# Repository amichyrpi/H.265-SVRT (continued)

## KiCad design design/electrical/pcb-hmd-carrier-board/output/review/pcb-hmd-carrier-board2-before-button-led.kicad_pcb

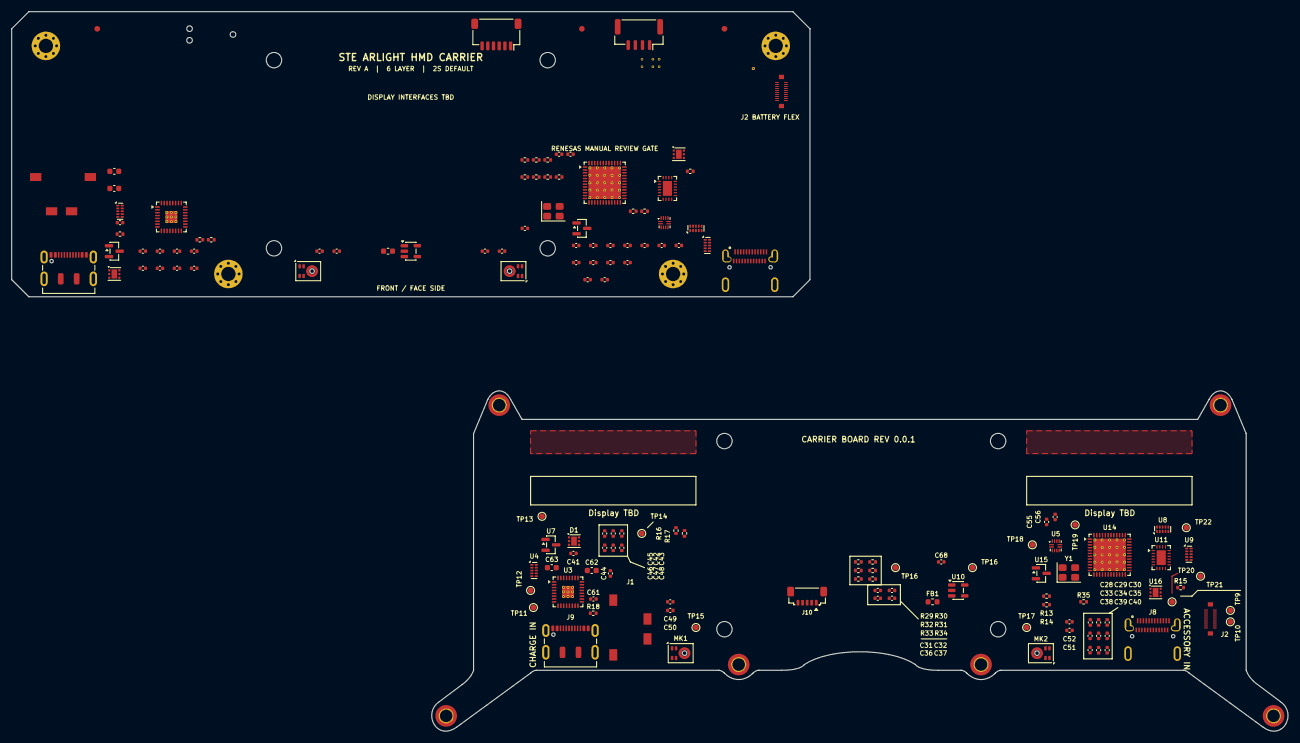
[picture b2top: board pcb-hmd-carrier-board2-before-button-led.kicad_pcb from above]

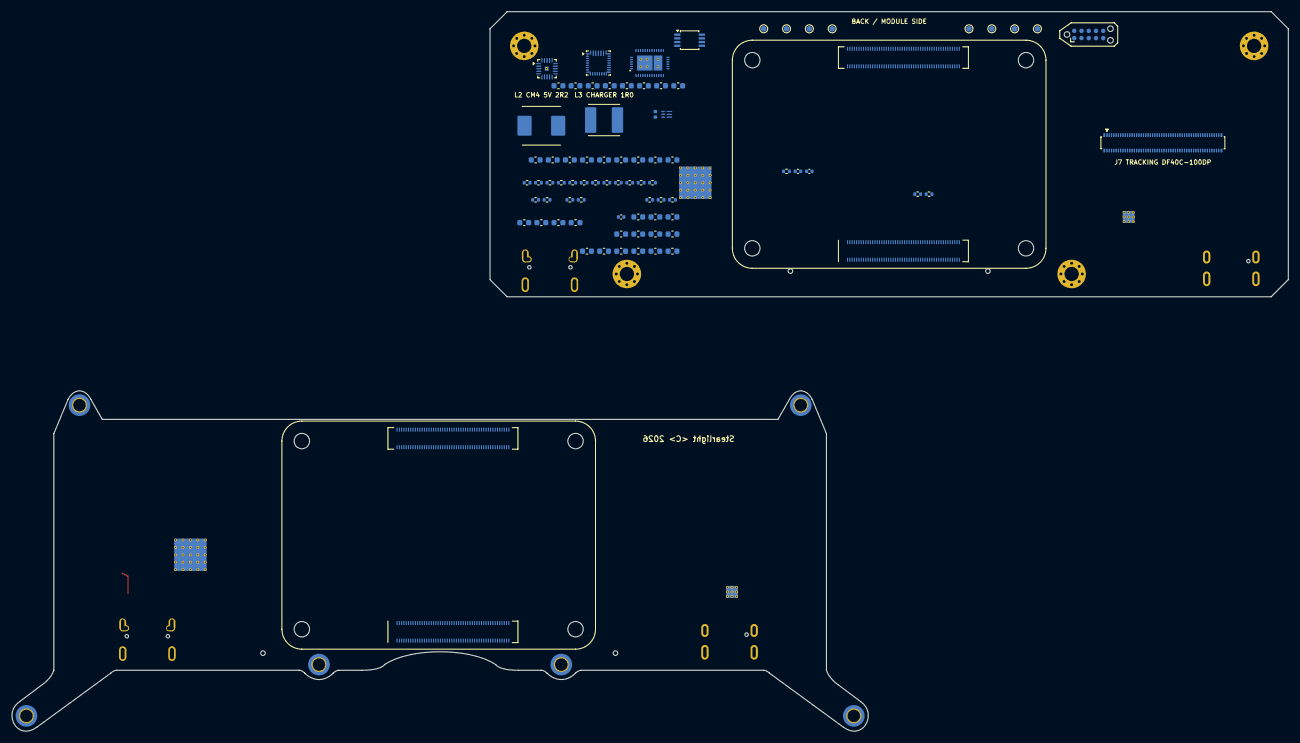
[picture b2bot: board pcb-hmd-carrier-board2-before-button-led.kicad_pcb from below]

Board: 6 copper layers, 223.8 x 126.2 mm, 232 parts (79 on the bottom side), 120 nets, no tracks yet.

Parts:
C1, C2, C3, C4, C5, C9, C10, C11, C13, C14, C19, C20, C21, C22, C23: 10u; C_0603_1608Metric
C6, C12, C15, C24, C25: 100n; C_0603_1608Metric
C7, C8: 330p; C_0603_1608Metric
C16: 4u7; C_0603_1608Metric
C17, C18: 47n; C_0603_1608Metric
C26: 1u; C_0603_1608Metric
C27: 47p; C_0603_1608Metric
C28, C28#2, C29, C29#2, C30, C30#2, C31, C31#2, C32, C32#2, C33, C33#2, C34, C34#2, C35, C35#2, C36, C36#2, C37, C37#2, C43, C43#2, C48, C48#2: 100n; C_0402_1005Metric
C38, C38#2, C44, C44#2, C45, C45#2, C46, C46#2, C47, C47#2: 10u; C_0402_1005Metric
C39, C39#2, C40, C40#2, C41, C41#2, C42, C42#2: 1u; C_0402_1005Metric
C49, C49#2, C50, C50#2, C51, C51#2, C52, C52#2: 1u C0G; C_0402_1005Metric
C53, C54, C55, C55#2, C56, C56#2: 100n PCIe AC; C_0402_1005Metric
C57, C58: 100u low-ESR; C_0603_1608Metric
C59, C60: 22u 25V; C_0603_1608Metric
C61, C61#2: 100n JACK MIC; C_0402_1005Metric
C62, C62#2: 47u HP LEFT; C_0603_1608Metric
C63, C63#2: 47u HP RIGHT; C_0603_1608Metric
C64: 4.7u 10V; C_0603_1608Metric
C65, C66: 10u 6.3V; C_0603_1608Metric
C67: 120p C0G; C_0402_1005Metric
C68, C68#2: 100n USB3 RESET; C_0402_1005Metric
D1, D1#2: TVS2200DRVR; WSON-6-1EP_2x2mm_P0.65mm_EP1x1.6mm
FB1, FB1#2: 600R@100MHz ferrite; L_0603_1608Metric
FID1, FID2, FID3: FIDUCIAL; Fiducial_1mm_Mask2mm
H1, H2, H3, H4: M2.5; MountingHole_2.5mm_Pad_Via
J1, J1#2: SJ-43514-SMT-TR; SameSky_SJ-43514-SMT-TR
J2, J2#2: BM28 BATTERY FLEX 5A + NTC/ID; Hirose_BM28B0.6-20DS_2-0.35V
J4: 5V GND PWM TACH; JST_GH_SM04B-GHS-TB_1x04-1MP_P1.25mm_Horizontal
J5: 3V3 GND SDA SCL INT GPIO; JST_SH_SM06B-SRSS-TB_1x06-1MP_P1.00mm_Horizontal
J6: TAG-CONNECT SERVICE PADS (NO FIT); Tag-Connect_TC2050-IDC-NL_2x05_P1.27mm_Vertical
J7: DF40C-100DP-0.4V(51) TRACKING; Hirose_DF40C-100DP-0.4V_2x50-1MP_P0.4mm
J8, J8#2: DX07S024JJ2R1300 ACCESSORY; JAE_DX07S024JJ2R1300
J9, J9#2: DX07S016JA1R1500 CHARGE/SERVICE; USB_C_Receptacle_JAE_DX07S016JA1R1500
J10: PROX SENSOR - SM05B-SURS-TF; JST_SUR_SM05B-SURS-TF_1x05-1MP_P0.80mm_Horizontal
L1: 0.47uH XFL4015-471MEC; L_0402_1005Metric
L2: SRP7050TA-2R2M 2.2uH 10A; Bourns_SRP7050TA
L3: SRP5030CA-1R0M 1uH 9A; Bourns_SRP5030CA
MK1, MK1#2, MK2, MK2#2: IM73A135V01; Infineon_PG-LLGA-5-2
Module1, Module1#2: CM4 2GB/16GB/Wireless; Raspberry-Pi-4-Compute-Module
R1: 220k; R_0402_1005Metric
R2: 30k; R_0402_1005Metric
R3: 5.23k ILIM; R_0402_1005Metric
R4: 137k ILIM; R_0402_1005Metric
R5, R6: 2.2k I2C; R_0402_1005Metric
R7, R8: 10k; R_0402_1005Metric
R9: 30.1k TS; R_0402_1005Metric
R10: 10k NTC; R_0402_1005Metric
R11: 100R BATP; R_0402_1005Metric
R12: 6.04k 2S; R_0402_1005Metric
R13, R13#2, R14, R14#2: 200k; R_0402_1005Metric
R15, R15#2: ILIM 1.5A TBD; R_0402_1005Metric
R16, R16#2, R17, R17#2: I2C 2.2k; R_0402_1005Metric
R18, R18#2: MICBIAS 2.7k; R_0402_1005Metric
R19: 75k 1V05 FB; R_0402_1005Metric
R20: 100k 1V05 FB; R_0402_1005Metric
R21: 100k 1V05 PG; R_0402_1005Metric
R22: 10k WIFI EN; R_0402_1005Metric
R23: 10k BT EN; R_0402_1005Metric
R24: 75k MODE; R_0402_1005Metric
R25: 51k MODE; R_0402_1005Metric
R26: 10k CLKREQ; R_0402_1005Metric
R27: 2.2k CHG SCL; R_0402_1005Metric
R28: 2.2k CHG SDA; R_0402_1005Metric
R29, R29#2: 10k OCI PU; R_0402_1005Metric
R30, R30#2: 1.6k RREF VERIFY; R_0402_1005Metric
R31, R31#2: 10k RESET PU; R_0402_1005Metric
R32, R32#2: 10k SPI CLK PD; R_0402_1005Metric
R33, R33#2: 10k SPI CS PD; R_0402_1005Metric
R34, R34#2: 10k SPI MISO PU; R_0402_1005Metric
R35, R35#2: 10k SPI MOSI PD; R_0402_1005Metric
TP1, TP9, TP10, TP11, TP12, TP13, TP14, TP15, TP16, TP16#2, TP17, TP18, TP19, TP20, TP21, TP22: CHG_STAT; TestPoint_Pad_D1.0mm
TP2: PGOOD_5V; TestPoint_Pad_D1.0mm
TP3: BAT_ID; TestPoint_Pad_D1.0mm
TP4: +5V_SYS; TestPoint_Pad_D1.0mm
TP5: +3V3; TestPoint_Pad_D1.0mm
TP6: +1V05_USB; TestPoint_Pad_D1.0mm
TP7: GND; TestPoint_Pad_D1.0mm
TP8: VBAT_SYS; TestPoint_Pad_D1.0mm
U1: TPS62825DMQR; Texas_DMQ0006A_VSON-HR-6_1.5x1.5mm
U2: TPS568230RJER; Texas_RJE0020A_VQFN-20-1EP_3x3mm_P0.45mm_EP0.675x0.76mm_The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
U3, U3#2: TLV320AIC3204IRHBR; Texas_RHB0032M_VQFN-32-1EP_5x5mm_P0.5mm_EP2.1x2.1mm_Thermal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
U4, U4#2: TPD4E05U06DQAR; USON-10_2.5x1.0mm_P0.5mm
U5, U5#2: TUSB320LAIRWBR; Texas_X2QFN-12_1.6x1.6mm_P0.4mm
U6: BQ25798RQMR; Texas_RQM0029A_VQFN-29_4x4mm_P0.4mm
U7, U7#2: TPD2EUSB30DRTR; SOT-23
U8, U8#2, U9, U9#2: TPD4EUSB30DQAR; USON-10_2.5x1.0mm_P0.5mm
U10, U10#2: TLV75528PDBVR; SOT-23-5
U11, U11#2: HD3SS3212IRKSR; Texas_RVC0020A_WQFN-20-1EP_3x4mm_P0.5mm_EP1.6x2.6mm
U12: TPS25751DREFR; Texas_REF0038A_WQFN-38_6x4mm_DualPad
U13: CAT24C512WI-GT3; TSSOP-8_3x3mm_P0.65mm
U14, U14#2: UPD720202K8-711-BAA-A; QFN-48-1EP_7x7mm_P0.5mm_EP5.7x5.7mm_ThermalVias
U15, U15#2: TLV803EA30DBZR; SOT-23
U16, U16#2: TPS2553-1DRVR; WSON-6-1EP_2x2mm_P0.65mm_EP1x1.6mm
Y1, Y1#2: 24MHz; Crystal_SMD_3225-4Pin_3.2x2.5mm

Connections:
+1V05_USB: C28.1, C28#2.1, C29.1, C29#2.1, C30.1, C30#2.1, C31.1, C31#2.1, C32.1, C32#2.1, C33.1, C33#2.1, C39.1, C39#2.1, C65.1, C66.1, C67.1, L1.2, R19.1, TP6.1, U14.6, U14.9, U14.21, U14.30, U14.33, U14.39, U14.42, U14#2.6, U14#2.9, U14#2.21, U14#2.30, U14#2.33, U14#2.39, U14#2.42
+2V8_MIC: C42.1, C42#2.1, MK1.2, MK1#2.2, MK2.2, MK2#2.2, U10.5, U10#2.5
+3V3: C3.1, C34.1, C34#2.1, C35.1, C35#2.1, C36.1, C36#2.1, C37.1, C37#2.1, C38.1, C38#2.1, C40.1, C40#2.1, C43.1, C43#2.1, C64.1, C68.1, C68#2.1, FB1.1, FB1#2.1, J5.1, J6.1, J10.4, Module1#2.78, Module1#2.84, Module1#2.86, R8.1, R13.1, R13#2.1, R14.1, R14#2.1, R16.1, R16#2.1, R17.1, R17#2.1, R21.1, R22.1, R23.1, R26.1, R29.1, R29#2.1, R31.1, R31#2.1, R34.1, R34#2.1, TP5.1, U1.1, U1.6, U3.6, U3.30, U3#2.6, U3#2.30, U5.3, U5.12, U5#2.3, U5#2.12, U11.6, U11#2.6, U12.38, U14.3, U14.12, U14.22, U14.25, U14.34, U14.43, U14#2.3, U14#2.12, U14#2.22, U14#2.25, U14#2.34, U14#2.43, U15.3, U15#2.3
+3V3_AUDIO: C41.1, C41#2.1, C45.1, C45#2.1, C48.1, C48#2.1, FB1.2, FB1#2.2, U3.26, U3#2.26, U10.1, U10.3, U10#2.1, U10#2.3
+5V_SYS: C57.1, C58.1, J4.1, L2.2, Module1#2.77, Module1#2.79, Module1#2.81, Module1#2.83, Module1#2.85, Module1#2.87, R1.1, TP4.1, U12.34, U12.35, U16.6, U16#2.6
AUDIO_1V8_LDO: C44.1, C44#2.1, U3.24, U3.29, U3#2.24, U3#2.29
AUDIO_MCLK: Module1#2.54, U3.1, U3#2.1
AUDIO_REF: C46.1, C46#2.1, U3.18, U3#2.18
AUDIO_RESET_N: Module1#2.34, U3.31, U3#2.31
BAT+: C24.1, J2.P1, R11.2, U6.22, U6.23
BATP: R11.1, U6.18
BAT_ID: J2.2, TP3.1
BST1: C17.1, U6.4
BST2: C18.1, U6.19
BST_5V: C25.1, U2.1
BT_ENABLE_N: Module1#2.91, R23.2
CC1: C7.1, J8#2.A5, J9#2.A5, U5.1, U5#2.1, U12.28
CC2: C8.1, J8#2.B5, J9#2.B5, U5.2, U5#2.2, U12.29
CHASSIS_GND: J8#2.SH, J9#2.SH
CHG_IRQ_N: R8.2, U6.21, U12.18
CHG_SCL: R27.2, U6.14, U12.17
CHG_SDA: R28.2, U6.15, U12.16
CHG_STAT: TP1.1, U6.1
CM4_EXT_RESET_N: J6.8, Module1#2.100
EMMC_BOOT_N: J6.7, Module1#2.93
FAN_PWM: J4.3, Module1#2.31
FAN_TACH: J4.4, Module1#2.30
FB_5V: C27.1, R1.2, R2.1, U2.14
GND: C1.2, C2.2, C3.2, C4.2, C5.2, C6.2, C7.2, C8.2, C9.2, C10.2, C11.2, C12.2, C13.2, C14.2, C15.2, C16.2, C19.2, C20.2, C21.2, C22.2, C23.2, C24.2, C26.2, C27.2, C28.2, C28#2.2, C29.2, C29#2.2, C30.2, C30#2.2, C31.2, C31#2.2, C32.2, C32#2.2, C33.2, C33#2.2, C34.2, C34#2.2, C35.2, C35#2.2, C36.2, C36#2.2, C37.2, C37#2.2, C38.2, C38#2.2, C39.2, C39#2.2, C40.2, C40#2.2, C41.2, C41#2.2, C42.2, C42#2.2, C43.2, C43#2.2, C44.2, C44#2.2, C45.2, C45#2.2, C46.2, C46#2.2, C47.2, C47#2.2, C48.2, C48#2.2, C57.2, C58.2, C59.2, C60.2, C64.2, C65.2, C66.2, C68.2, C68#2.2, D1.1, D1.2, D1.3, D1.7, D1#2.1, D1#2.2, D1#2.3, D1#2.7, J1#2.4, J2.P2, J4.2, J5.2, J6.2, J6.10, J8#2.A1, J8#2.A12, J8#2.B1, J8#2.B12, J9#2.A1, J9#2.A12, J9#2.B1, J9#2.B12, J10.5, MK1.4, MK1.5, MK1#2.4, MK1#2.5, MK2.4, MK2.5, MK2#2.4, MK2#2.5, Module1#2.1, Module1#2.2, Module1#2.7, Module1#2.8, Module1#2.13, Module1#2.14, Module1#2.22, Module1#2.23, Module1#2.32, Module1#2.33, Module1#2.42, Module1#2.43, Module1#2.52, Module1#2.53, Module1#2.59, Module1#2.60, Module1#2.65, Module1#2.66, Module1#2.71, Module1#2.74, Module1#2.98, Module1#2.101, Module1#2.107, Module1#2.108, Module1#2.113, Module1#2.114, Module1#2.119, Module1#2.120, Module1#2.125, Module1#2.126, Module1#2.131, Module1#2.132, Module1#2.137, Module1#2.138, Module1#2.144, Module1#2.150, Module1#2.155, Module1#2.156, Module1#2.161, Module1#2.162, Module1#2.167, Module1#2.168, Module1#2.173, Module1#2.174, Module1#2.179, Module1#2.180, Module1#2.185, Module1#2.186, Module1#2.191, Module1#2.192, Module1#2.197, Module1#2.198, R2.2, R4.2, R9.2, R10.2, R12.2, R15.2, R15#2.2, R20.2, R25.2, R30.2, R30#2.2, R32.2, R32#2.2, R33.2, R33#2.2, R35.2, R35#2.2, TP7.1, U1.4, U2.7, U2.8, U2.13, U2.18, U2.21, U3.7, U3.12, U3.17, U3.28, U3#2.7, U3#2.12, U3#2.17, U3#2.28, U4.3, U4.5, U4.8, U4#2.3, U4#2.5, U4#2.8, U5.5, U5.10, U5.11, U5#2.5, U5#2.10, U5#2.11, U6.10, U6.11, U6.12, U6.13, U6.27, U7.3, U7#2.3, U8.3, U8.8, U8#2.3, U8#2.8, U9.3, U9.8, U9#2.3, U9#2.8, U10.2, U10#2.2, U11.2, U11.5, U11.11, U11.20, U11#2.2, U11#2.5, U11#2.11, U11#2.20, U12.11, U12.12, U12.14, U12.31, U12.39, U13.1, U13.2, U13.3, U13.4, U13.7, U14.27, U14.49, U14#2.27, U14#2.49, U15.1, U15#2.1, U16.5, U16.7, U16#2.5, U16#2.7, Y1.2, Y1.4, Y1#2.2, Y1#2.4
HP_L: C62.2, C62#2.2, J1#2.2, U4.1, U4#2.1
HP_L_CODEC: C62.1, C62#2.1, U3.25, U3#2.25
HP_R: C63.2, C63#2.2, J1#2.3, U4.2, U4#2.2
HP_R_CODEC: C63.1, C63#2.1, U3.27, U3#2.27
I2C_SCL: J5.4, J6.4, J10.3, Module1#2.56, R16.2, R16#2.2, U3.9, U3#2.9, U5.8, U5#2.8
I2C_SDA: J5.3, J6.3, J10.2, Module1#2.58, R17.2, R17#2.2, U3.10, U3#2.10, U5.7, U5#2.7
I2Ct_SCL: R6.2, U12.9, U13.6
I2Ct_SDA: R5.2, U12.8, U13.5
I2S_BCLK: Module1#2.49, U3.2, U3#2.2
I2S_DIN: Module1#2.27, U3.5, U3#2.5
I2S_DOUT: Module1#2.25, U3.4, U3#2.4
I2S_LRCLK: Module1#2.26, U3.3, U3#2.3
ILIM_HIZ: R3.2, R4.1, U6.17
JACK_MIC: C61.1, C61#2.1, J1#2.1, R18.2, R18#2.2, U4.4, U4#2.4
JACK_MIC_CODEC: C61.2, C61#2.2, U3.21, U3#2.21
LDO_1V5: C2.1, U12.2, U12.3, U12.4
LDO_3V3: C1.1, R5.1, R6.1, R7.1, R27.1, R28.1, U12.1, U13.8
MICBIAS: C47.1, C47#2.1, R18.1, R18#2.1, U3.19, U3#2.19
MIC_L_N: C50.2, C50#2.2, U3.16, U3#2.16
MIC_L_P: C49.2, C49#2.2, U3.15, U3#2.15
MIC_L_RAW_N: C50.1, C50#2.1, MK1.3, MK1#2.3
MIC_L_RAW_P: C49.1, C49#2.1, MK1.1, MK1#2.1
MIC_R_N: C52.2, C52#2.2, U3.13, U3#2.13
MIC_R_P: C51.2, C51#2.2, U3.14, U3#2.14
MIC_R_RAW_N: C52.1, C52#2.1, MK2.3, MK2#2.3
MIC_R_RAW_P: C51.1, C51#2.1, MK2.1, MK2#2.1
MODE_5V: R24.2, R25.1, U2.15
PCIE_CLKREQ_N: Module1#2.102, R26.2, U14.10, U14#2.10
PCIE_CLK_N: Module1#2.112, U14.2, U14#2.2
PCIE_CLK_P: Module1#2.110, U14.1, U14#2.1
PCIE_RST_N: Module1#2.109, U14.47, U14#2.47
PCIE_RX_N: C56.2, C56#2.2, Module1#2.118
PCIE_RX_P: C55.2, C55#2.2, Module1#2.116
PCIE_RX_USB3_N: C56.1, C56#2.1, U14.5, U14#2.5
PCIE_RX_USB3_P: C55.1, C55#2.1, U14.4, U14#2.4
PCIE_TX_CM4_N: C54.1, Module1#2.124
PCIE_TX_CM4_P: C53.1, Module1#2.122
PCIE_TX_N: C54.2, U14.8, U14#2.8
PCIE_TX_P: C53.2, U14.7, U14#2.7
PD_IRQ_N: R7.2, U12.10
PGOOD_5V: TP2.1, U2.9
PMID: C13.1, C14.1, C15.1, U6.29
PPHV: C4.1, C5.1, C6.1, U6.2, U6.3, U6.8, U6.9, U12.20, U12.21, U12.22
PROG: R12.1, U6.20
PROX_GPIO: J5.6, Module1#2.41
PROX_INT: J5.5, J10.1, Module1#2.47
REGN: C16.1, R3.1, U6.5
RUN_PG: J6.9, Module1#2.92
SPI_CLK: R32.1, R32#2.1, U14.15, U14#2.15
SPI_CS_N: R33.1, R33#2.1, U14.14, U14#2.14
SPI_MISO: R34.2, R34#2.2, U14.13, U14#2.13
SPI_MOSI: R35.1, R35#2.1, U14.16, U14#2.16
SW1: C17.2, L3.1, U6.28
SW2: C18.2, L3.2, U6.26
SW_5V: C25.2, L2.1, U2.6, U2.19, U2.20
TS: J2.1, R9.1, R10.1, U6.16
TYPEC_ATTACHED_N: R14.2, R14#2.2, U5.9, U5#2.9, U16.4, U16#2.4
TYPEC_FLIP: Module1#2.48, U11.9, U11#2.9
TYPEC_INT_N: Module1#2.46, R13.2, R13#2.2, U5.6, U5#2.6
UART_RX: J6.6, Module1#2.51
UART_TX: J6.5, Module1#2.55
USB1V05_FB: C67.2, R19.2, R20.1, U1.3
USB1V05_PG: R21.2, U1.2
USB1V05_SW: L1.1, U1.5
USB2_HOST_DM: J8#2.A7, J8#2.B7, U7.2, U7#2.2, U14.36, U14#2.36
USB2_HOST_DP: J8#2.A6, J8#2.B6, U7.1, U7#2.1, U14.35, U14#2.35
USB2_SERVICE_DM: J9#2.A7, J9#2.B7, Module1#2.103, U12.27
USB2_SERVICE_DP: J9#2.A6, J9#2.B6, Module1#2.105, U12.26
USB3_POR_N: R31.2, R31#2.2, U14.11, U14#2.11, U15.2, U15#2.2
USB3_RREF: R30.1, R30#2.1, U14.26, U14#2.26
USB3_RX_N: U11.8, U11#2.8, U14.32, U14#2.32
USB3_RX_P: U11.7, U11#2.7, U14.31, U14#2.31
USB3_TX_N: U11.4, U11#2.4, U14.29, U14#2.29
USB3_TX_P: U11.3, U11#2.3, U14.28, U14#2.28
USB3_XT1: U14.24, U14#2.24, Y1.1, Y1#2.1
USB3_XT2: U14.23, U14#2.23, Y1.3, Y1#2.3
USB_C_RX1_N: J8#2.B10, U8.5, U8#2.5, U11.16, U11#2.16
USB_C_RX1_P: J8#2.B11, U8.4, U8#2.4, U11.17, U11#2.17
USB_C_RX2_N: J8#2.A10, U9.5, U9#2.5, U11.12, U11#2.12
USB_C_RX2_P: J8#2.A11, U9.4, U9#2.4, U11.13, U11#2.13
USB_C_TX1_N: J8#2.A3, U8.2, U8#2.2, U11.18, U11#2.18
USB_C_TX1_P: J8#2.A2, U8.1, U8#2.1, U11.19, U11#2.19
USB_C_TX2_N: J8#2.B3, U9.2, U9#2.2, U11.14, U11#2.14
USB_C_TX2_P: J8#2.B2, U9.1, U9#2.1, U11.15, U11#2.15
USB_ILIM: R15.1, R15#2.1, U16.2, U16#2.2
USB_OC_N: R29.2, R29#2.2, U14.19, U14#2.19, U16.3, U16#2.3
VBAT_SYS: C19.1, C20.1, C21.1, C22.1, C23.1, C59.1, C60.1, TP8.1, U2.2, U2.3, U2.4, U2.5, U2.12, U6.25
VBUS_CHARGE: C9.1, C10.1, C11.1, C12.1, D1.4, D1.5, D1.6, D1#2.4, D1#2.5, D1#2.6, J9#2.A4, J9#2.A9, J9#2.B4, J9#2.B9, U12.23, U12.24, U12.25, U12.32, U12.33
VBUS_USB_HOST: J8#2.A4, J8#2.A9, J8#2.B4, J8#2.B9, U16.1, U16#2.1
VCC_5V: C26.1, R24.1, U2.17
WIFI_ENABLE_N: Module1#2.89, R22.2
